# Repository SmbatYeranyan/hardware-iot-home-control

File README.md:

# hardware-iot-home-control

**Files**

Contains Eagle files for the board design

**Description**

Controlling sub GHz (433 MHz) electronic switches in the house with mobile &amp; wearable app.

**Other project parts**

Hardware part of the project [**repo**](https://github.com/SmbatYeranyan/hardware-iot-home-control)

Android part of the project [**repo**](https://github.com/bernardpletikosa/android-iot-home-control)

Server part of the project [**repo**](https://github.com/SmbatYeranyan/nodejs-iot-home-control)

Firmware part of the project [**repo**](https://github.com/SmbatYeranyan/firmware-iot-home-control)

**Board**

**Showcase video**

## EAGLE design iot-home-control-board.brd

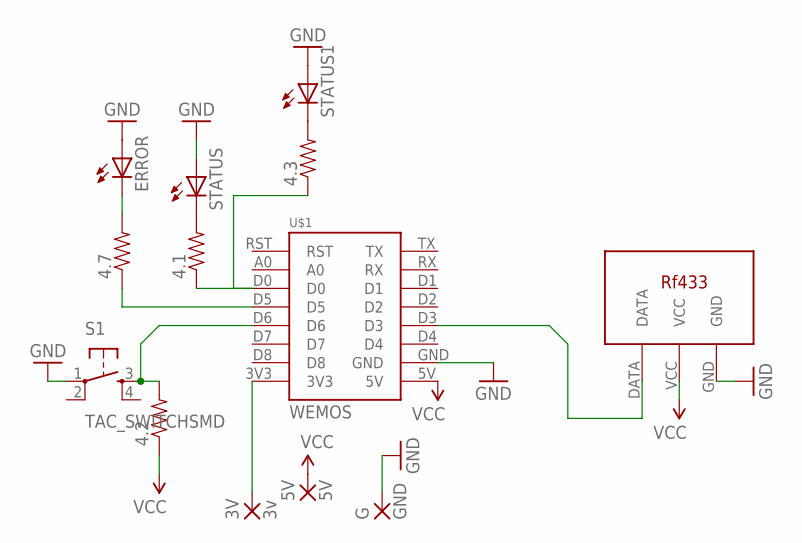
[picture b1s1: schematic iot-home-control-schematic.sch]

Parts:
3V: 3v; 2,15/1,0
4.1, 4.2, 4.3, 4.7: RESISTOR0805-RES; 0805
5V: 5V; 2,15/1,0
ERROR: LEDCHIPLED_0805; CHIPLED_0805
G: GND; 2,15/1,0
S1: TAC_SWITCHSMD; TACTILE-SWITCH-SMD
STATUS, STATUS1: LEDCHIPLED_0805; CHIPLED_0805
U$1: WEMOS
U$2: RF433; 433MHZ

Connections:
GND: ERROR.A, G.1, S1.1, STATUS.A, STATUS1.A, U$1.GND, U$2.GND
unnamed: U$1.D3, U$2.DATA
unnamed: 4.7.1, U$1.D5
unnamed: 4.7.2, ERROR.C
unnamed: 4.1.1, 4.3.1, U$1.D0
unnamed: 4.1.2, STATUS.C
unnamed: 3V.1, U$1.3V3
unnamed: 4.3.2, STATUS1.C
unnamed: 4.2.2, S1.3, U$1.D6
VCC: 4.2.1, 5V.1, U$1.5V, U$2.VCC

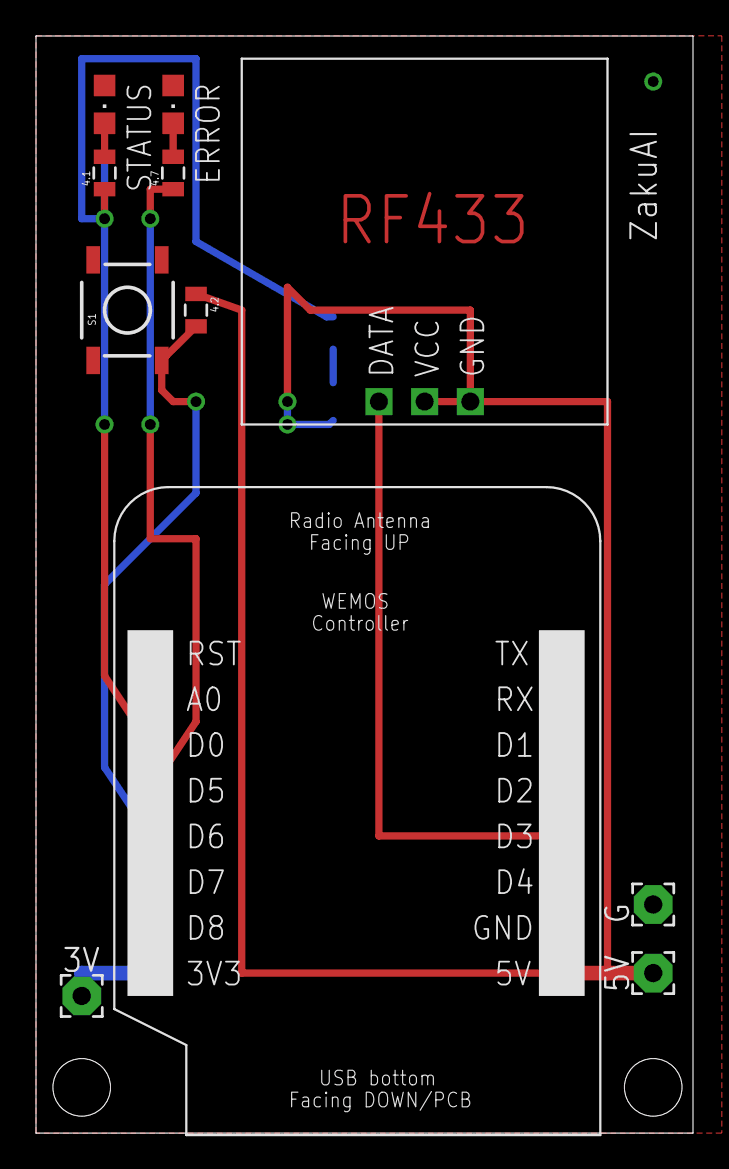
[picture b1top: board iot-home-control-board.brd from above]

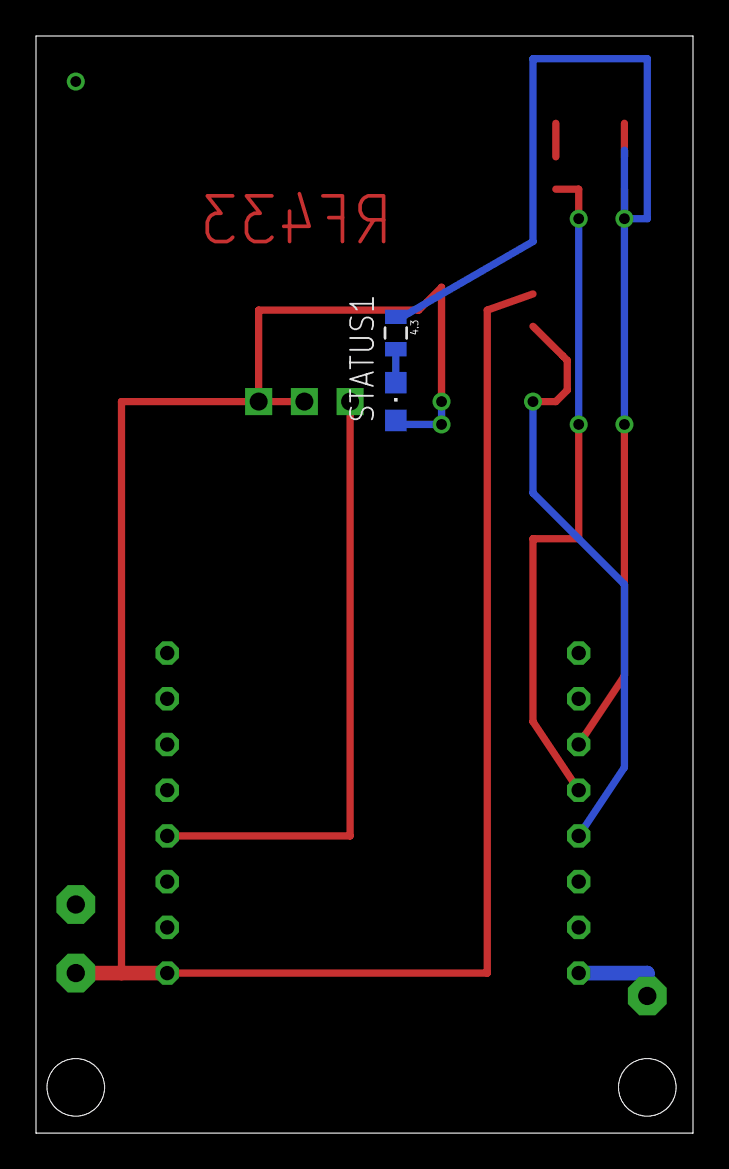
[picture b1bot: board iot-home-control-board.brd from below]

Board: 2 copper layers, 36.5 x 61.0 mm, 13 parts (2 on the bottom side), 10 nets.

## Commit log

2016-07-23 Added eagle files for schematic and board
2016-07-23 vid thumb
2016-11-02 Create LICENSE

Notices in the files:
parts and their libraries:
SparkFun-Passives: Licensing: Creative Commons ShareAlike 4.0 International - https://creativecommons.org/licenses/by-sa/4.0
SparkFun: Licensing: CC v3.0 Share-Alike You are welcome to use this library for commercial purposes.
